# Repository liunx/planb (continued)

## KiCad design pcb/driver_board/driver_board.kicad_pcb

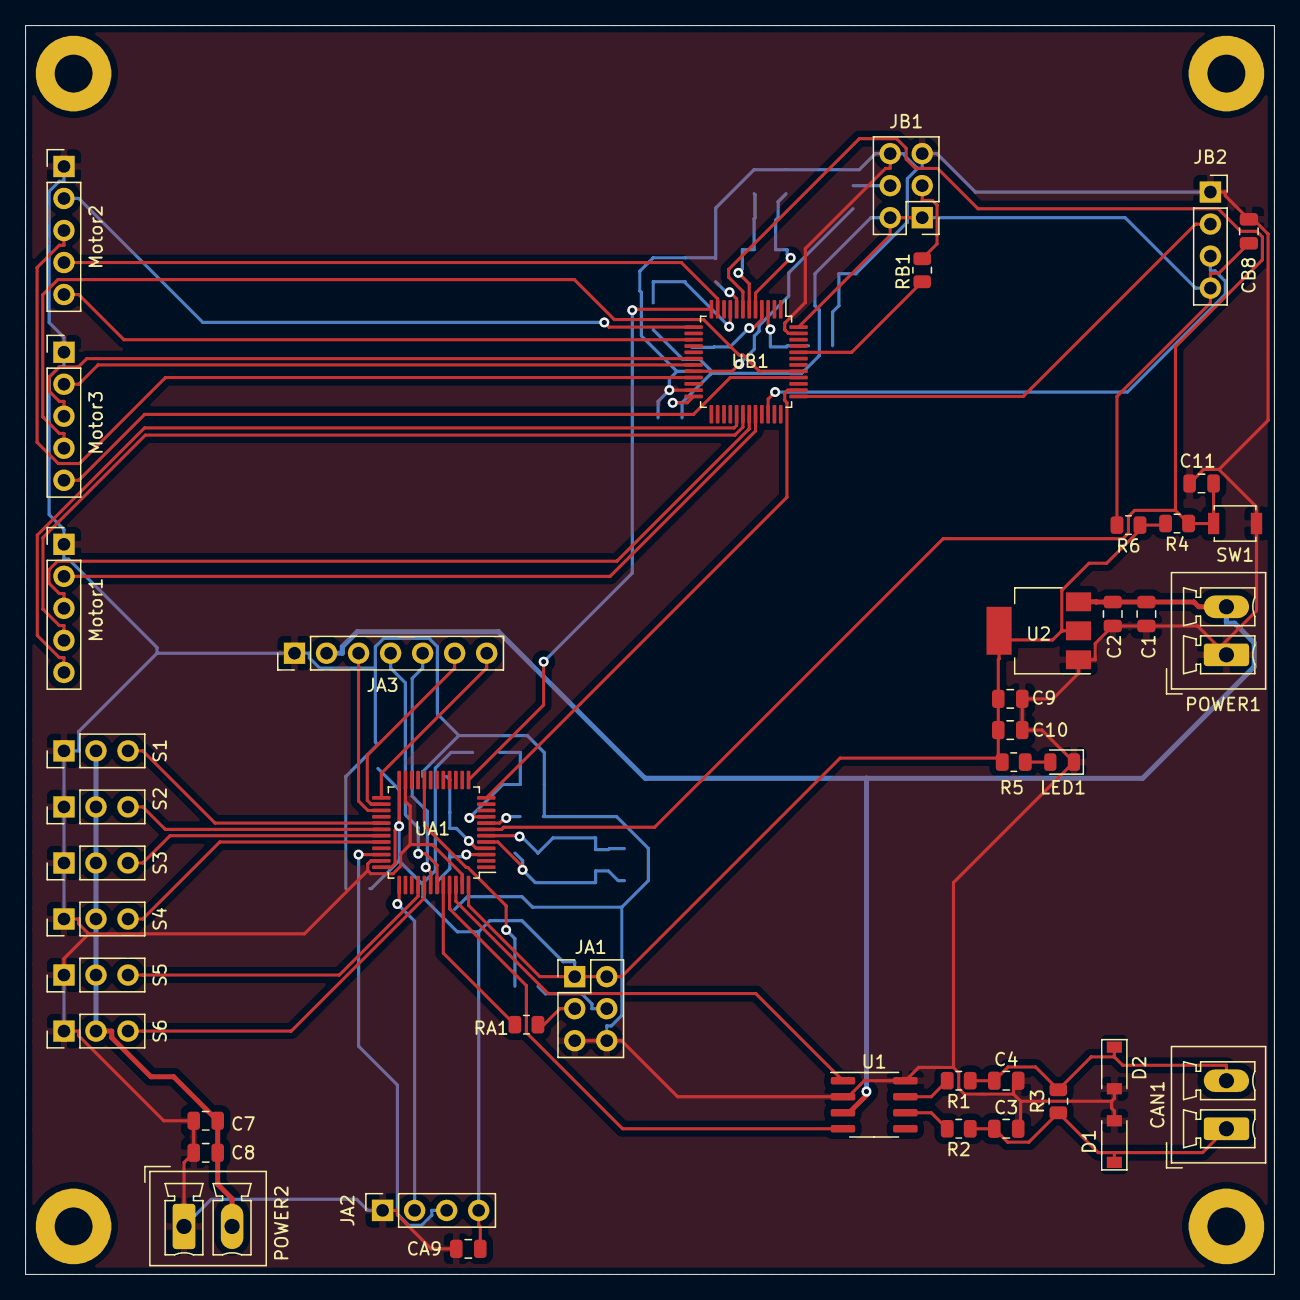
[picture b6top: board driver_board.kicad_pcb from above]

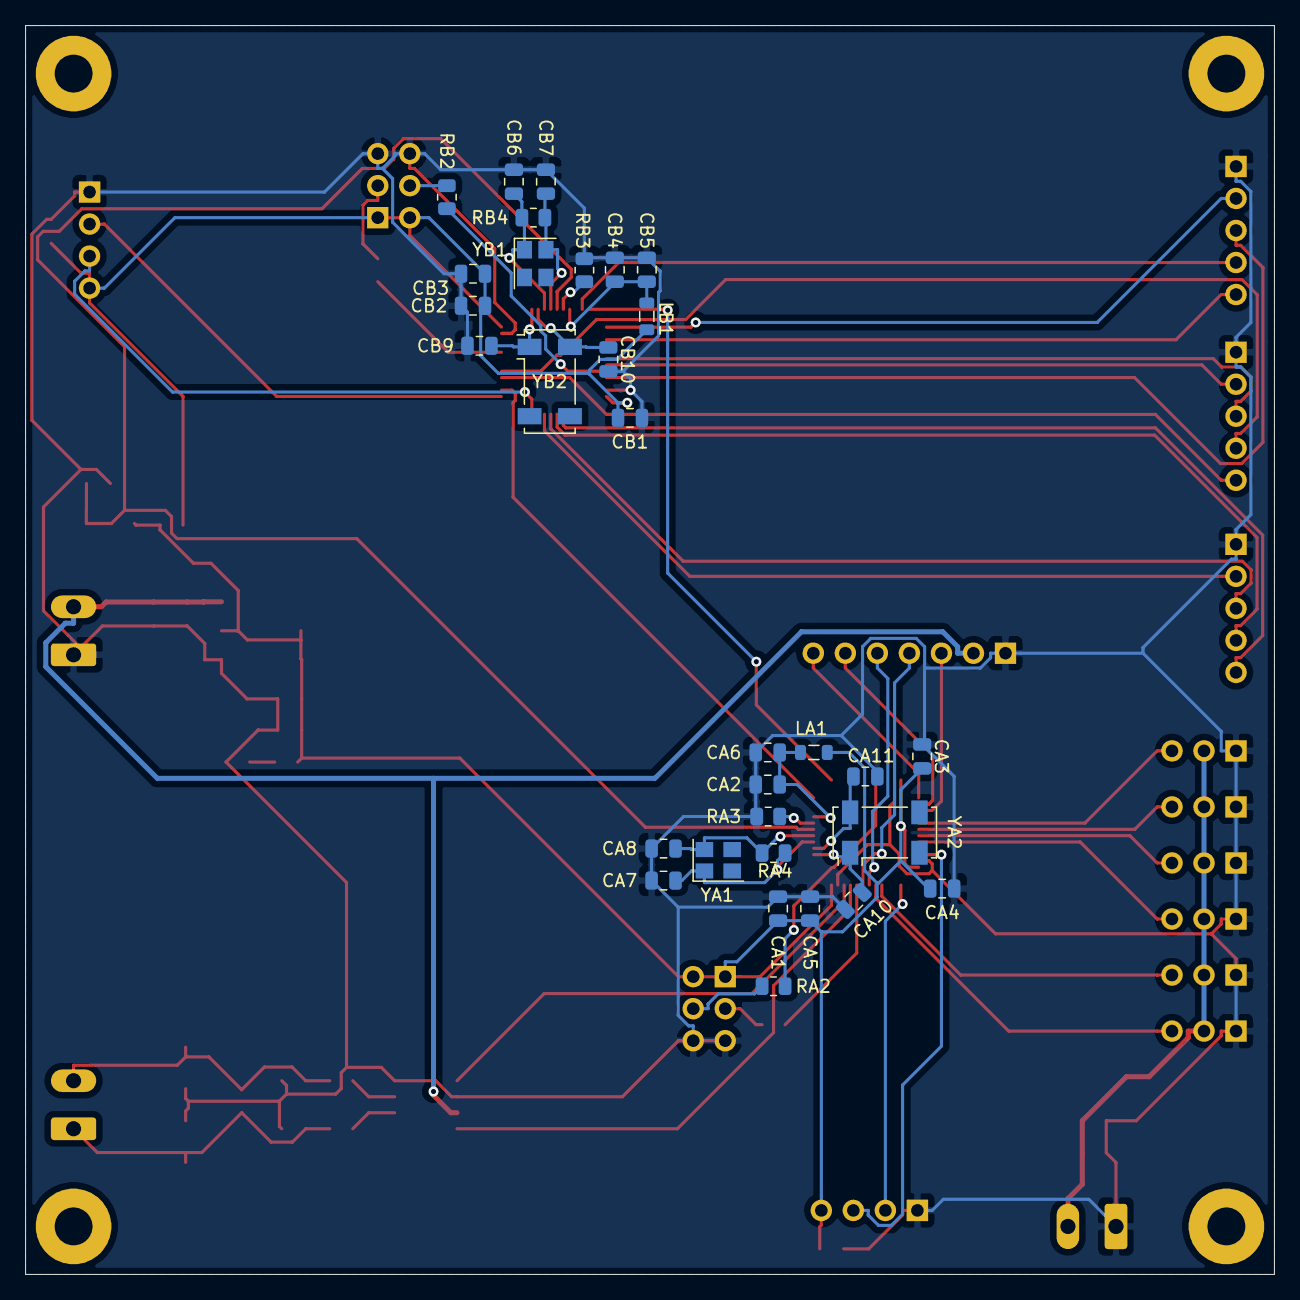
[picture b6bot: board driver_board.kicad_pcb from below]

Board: 2 copper layers, 99.1 x 99.1 mm, 79 parts (31 on the bottom side), 62 nets.

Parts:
C1, C7, C9: 10uF; C_0805_2012Metric
C2, C8, C10: 0.1uF; C_0805_2012Metric
C3, C4: 22pF; C_0805_2012Metric
C11: 10pF; C_0805_2012Metric
CA1: 4.7uF; C_0805_2012Metric
CA2: 10nF; C_0805_2012Metric
CA3, CA4, CA5, CA9: 0.1uF; C_0805_2012Metric
CA6: 1uF; C_0805_2012Metric
CA7, CA8, CA10, CA11: 20pF; C_0805_2012Metric
CAN1: Conn_01x02; PhoenixContact_MCV_1,5_2-G-3.81_1x02_P3.81mm_Vertical
CB1, CB3, CB8: 0.1uF; C_0805_2012Metric
CB2: 4.7uF; C_0805_2012Metric
CB4: 1uF; C_0805_2012Metric
CB5: 10nF; C_0805_2012Metric
CB6, CB7, CB9, CB10: 20pF; C_0805_2012Metric
D1, D2: 1N5817; D_SOD-123
JA1: Conn_02x03_Odd_Even; PinHeader_2x03_P2.54mm_Vertical
JA2: Conn_01x04; PinSocket_1x04_P2.54mm_Vertical
JA3: Conn_01x07; PinHeader_1x07_P2.54mm_Vertical
JB1: Conn_02x03_Odd_Even; PinHeader_2x03_P2.54mm_Vertical
JB2: Conn_01x04; PinSocket_1x04_P2.54mm_Vertical
LA1: 10uH; L_0805_2012Metric
LB1: 10uH; L_0805_2012Metric
LED1: LED; LED_0805_2012Metric
Motor1, Motor2, Motor3: Conn_01x05; PinHeader_1x05_P2.54mm_Vertical
POWER1, POWER2: Conn_01x02; PhoenixContact_MCV_1,5_2-G-3.81_1x02_P3.81mm_Vertical
Pad1, Pad2, Pad3, Pad4: MountingHole_3mm_Pad
R1, R2: 33R; R_0805_2012Metric
R3: 120R; R_0805_2012Metric
R4: 10K; R_0805_2012Metric
R5: 510R; R_0805_2012Metric
R6: 0R; R_0805_2012Metric
RA1, RA2: 100K; R_0805_2012Metric
RA3: 0R; R_0805_2012Metric
RA4: 10M; R_0805_2012Metric
RB1, RB2: 100K; R_0805_2012Metric
RB3: 0R; R_0805_2012Metric
RB4: 10M; R_0805_2012Metric
S1, S2, S3, S4, S5, S6: Conn_01x03; PinHeader_1x03_P2.54mm_Vertical
SW1: SW_Push; SW_SPST_B3U-1000P
U1: TJA1051T; SOIC-8_3.9x4.9mm_P1.27mm
U2: AMS1117-3.3; SOT-223-3_TabPin2
UA1: STM32F103C6Tx; LQFP-48_7x7mm_P0.5mm
UB1: STM32F031C6Tx; LQFP-48_7x7mm_P0.5mm
YA1: 8M; Crystal_SMD_Abracon_ABM8G-4Pin_3.2x2.5mm
YA2: 32768HZ; Crystal_SMD_Abracon_ABS25-4Pin_8.0x3.8mm
YB1: 8M; Crystal_SMD_Abracon_ABM8G-4Pin_3.2x2.5mm
YB2: 32768HZ; Crystal_SMD_Abracon_ABS25-4Pin_8.0x3.8mm

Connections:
+3.3V: C9.1, C10.1, CA1.1, CA3.1, CA4.1, CA5.1, CA9.1, JA1.1, JA1.2, JA2.4, LA1.2, R4.2, R5.2, R6.1, U2.2, UA1.24, UA1.36, UA1.48
+3.3V_F031: CB1.1, CB2.1, CB3.1, CB8.1, JB1.1, JB1.2, JB2.4, LB1.2, R6.2, UB1.24, UB1.48
+5V: C1.1, C2.1, JA3.2, POWER1.2, U1.3, U2.3
+VDC: C7.1, C8.1, POWER2.2, S1.2, S2.2, S3.2, S4.2, S5.2, S6.2
/CANH: C4.1, CAN1.2, D2.1, R1.1, R3.2
/CANL: C3.1, CAN1.1, D1.1, R2.1, R3.1
/Sheet6121200E/3.3VA: CA2.1, CA6.1, LA1.1, UA1.9
/Sheet6121200E/AUX: JA3.3, UA1.27
/Sheet6121200E/BOOT0: RA1.2, UA1.44
/Sheet6121200E/BOOT1: RA2.1, UA1.20
/Sheet6121200E/GNDA: RA3.2, UA1.8
/Sheet6121200E/MD0: JA3.7, UA1.25
/Sheet6121200E/MD1: JA3.6, UA1.26
/Sheet6121200E/RCC_OSC32_IN: CA10.2, UA1.3, YA2.1
/Sheet6121200E/RCC_OSC32_OUT: CA11.2, UA1.4, YA2.4
/Sheet6121200E/RCC_OSC_IN: CA7.2, RA4.2, UA1.5, YA1.1
/Sheet6121200E/RCC_OSC_OUT: CA8.2, RA4.1, UA1.6, YA1.4
/Sheet6121200E/SYS_JTCK-SWCL: JA2.2, UA1.37
/Sheet6121200E/SYS_JTMS-SWDIO: JA2.3, UA1.34
/Sheet6121200E/TIM1_CH1: S1.3, UA1.29
/Sheet6121200E/TIM1_CH2: S2.3, UA1.30
/Sheet6121200E/TIM1_CH3: S3.3, UA1.31
/Sheet6121200E/TIM1_CH4: S4.3, UA1.32
/Sheet6121200E/TIM3_CH1: S5.3, UA1.40
/Sheet6121200E/TIM3_CH2: S6.3, UA1.41
/Sheet6121200E/USART1_RX: JA3.4, UA1.43
/Sheet6121200E/USART1_TX: JA3.5, UA1.42
/sheet61233186/3.3VA: CB4.1, CB5.1, LB1.1, UB1.9
/sheet61233186/BOOT0: RB1.2, UB1.44
/sheet61233186/BOOT1: RB2.1, UB1.20
/sheet61233186/F031_RX: UA1.12, UB1.38
/sheet61233186/F031_TX: UA1.13, UB1.12
/sheet61233186/GNDA: RB3.2, UB1.8
/sheet61233186/RCC_OSC32_IN: CB9.2, UB1.3, YB2.1
/sheet61233186/RCC_OSC32_OUT: CB10.2, UB1.4, YB2.4
/sheet61233186/RCC_OSC_IN: CB6.2, RB4.2, UB1.5, YB1.1
/sheet61233186/RCC_OSC_OUT: CB7.2, RB4.1, UB1.6, YB1.4
/sheet61233186/SYS_JTCK-SWCL: JB2.2, UB1.37
/sheet61233186/SYS_JTMS-SWDIO: JB2.3, UB1.34
/sheet61233186/TIM1_CH1: Motor1.5, UB1.29
/sheet61233186/TIM1_CH2: Motor1.4, UB1.30
/sheet61233186/TIM1_CH3: Motor1.3, UB1.31
/sheet61233186/TIM1_CH4: Motor1.2, UB1.32
/sheet61233186/TIM2_CH1: Motor2.5, UB1.15
/sheet61233186/TIM2_CH2: Motor2.4, UB1.11
/sheet61233186/TIM2_CH3: Motor2.3, UB1.21
/sheet61233186/TIM2_CH4: Motor2.2, UB1.13
/sheet61233186/TIM3_CH1: Motor3.5, UB1.40
/sheet61233186/TIM3_CH2: Motor3.4, UB1.41
/sheet61233186/TIM3_CH3: Motor3.3, UB1.18
/sheet61233186/TIM3_CH4: Motor3.2, UB1.19
CAN_RX: U1.4, UA1.45
CAN_TX: U1.1, UA1.46
GND: C1.2, C2.2, C3.2, C4.2, C7.2, C8.2, C9.2, C10.2, C11.2, CA1.2, CA2.2, CA3.2, CA4.2, CA5.2, CA6.2, CA7.1, CA8.1, CA9.2, CA10.1, CA11.1, CB1.2, CB2.2, CB3.2, CB4.2, CB5.2, CB6.1, CB7.1, CB8.2, CB9.1, CB10.1, D1.2, D2.2, JA1.5, JA1.6, JA2.1, JA3.1, JB1.5, JB1.6, JB2.1, LED1.1, Motor1.1, Motor2.1, Motor3.1, POWER1.1, POWER2.1, RA3.1, RB3.1, S1.1, S2.1, S3.1, S4.1, S5.1, S6.1, SW1.1, U1.2, U1.8, U2.1, UA1.23, UA1.35, UA1.47, UB1.23, UB1.47
unnamed: JA1.3, RA1.1
unnamed: JA1.4, RA2.2
unnamed: JB1.3, RB1.1
unnamed: JB1.4, RB2.2
unnamed: LED1.2, R5.1
unnamed: R1.2, U1.7
unnamed: R2.2, U1.6
RESET: C11.1, R4.1, SW1.2, UA1.7, UB1.7

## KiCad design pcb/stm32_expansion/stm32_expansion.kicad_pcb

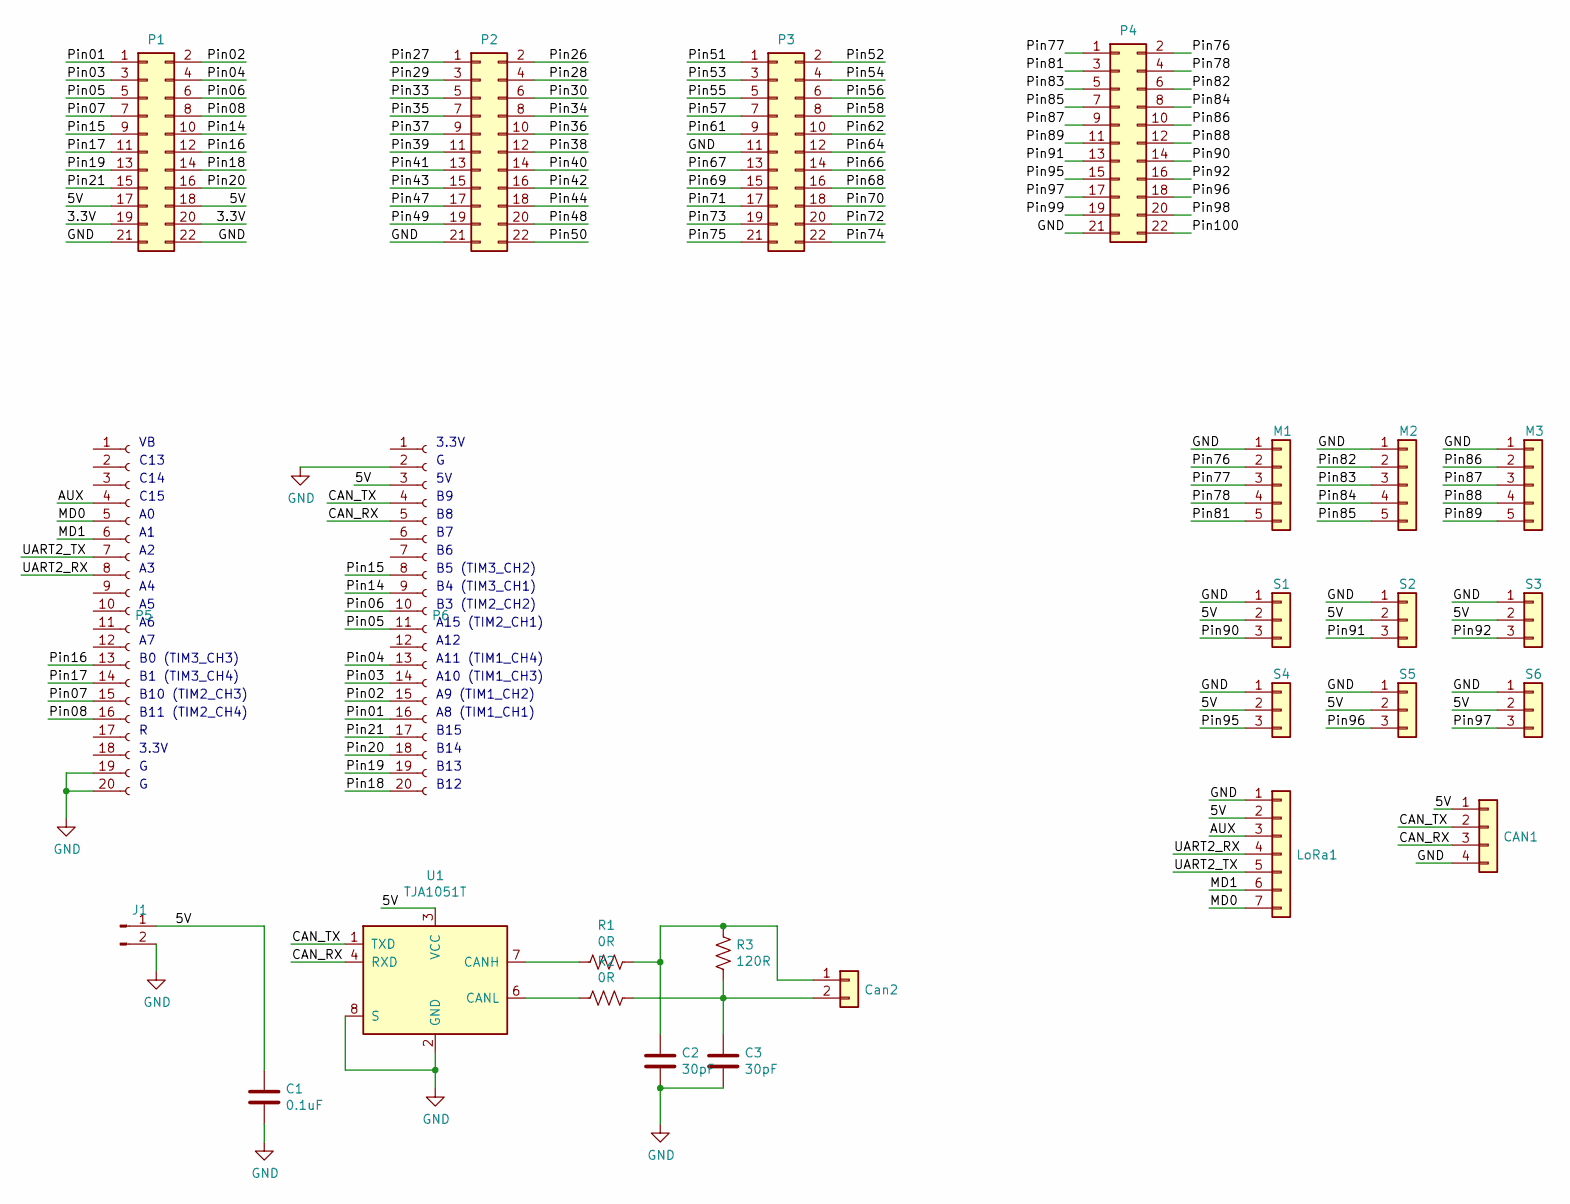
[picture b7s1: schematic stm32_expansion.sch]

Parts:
C1: 0.1uF; CP_EIA-2012-12_Kemet-R
C2, C3: 30pF; CP_EIA-2012-12_Kemet-R
CAN1: Conn_01x04; PinSocket_1x04_P2.54mm_Vertical
Can2: Conn_01x02; PinSocket_1x02_P2.54mm_Vertical
J1: Conn_01x02_Male; PinSocket_1x02_P2.54mm_Vertical
LoRa1: Conn_01x07; PinSocket_1x07_P2.54mm_Vertical
M1, M2, M3: Conn_01x05; PinSocket_1x05_P2.54mm_Vertical
P1, P2, P3, P4: Conn_02x11_Odd_Even; PinSocket_2x11_P2.54mm_Vertical
P5, P6: Conn_01x20_Female; PinSocket_1x20_P2.54mm_Vertical
R1, R2: 0R; R_0805_2012Metric
R3: 120R; R_0805_2012Metric
S1, S2, S3, S4, S5, S6: Conn_01x03; PinSocket_1x03_P2.54mm_Vertical
U1: TJA1051T; SOIC-8_3.9x4.9mm_P1.27mm

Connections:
/3.3V: P1.19, P1.20
/5V: C1.1, CAN1.1, J1.1, LoRa1.2, P1.17, P1.18, P6.3, S1.2, S2.2, S3.2, S4.2, S5.2, S6.2, U1.3 (VCC)
/AUX: LoRa1.3, P5.4
/CAN_RX: CAN1.3, P6.5, U1.4 (RXD)
/CAN_TX: CAN1.2, P6.4, U1.1 (TXD)
/MD0: LoRa1.7, P5.5
/MD1: LoRa1.6, P5.6
/Pin01: P1.1, P6.16
/Pin02: P1.2, P6.15
/Pin03: P1.3, P6.14
/Pin04: P1.4, P6.13
/Pin05: P1.5, P6.11
/Pin06: P1.6, P6.10
/Pin07: P1.7, P5.15
/Pin08: P1.8, P5.16
/Pin14: P1.10, P6.9
/Pin15: P1.9, P6.8
/Pin16: P1.12, P5.13
/Pin17: P1.11, P5.14
/Pin18: P1.14, P6.20
/Pin19: P1.13, P6.19
/Pin20: P1.16, P6.18
/Pin21: P1.15, P6.17
/Pin26: P2.2
/Pin27: P2.1
/Pin28: P2.4
/Pin29: P2.3
/Pin30: P2.6
/Pin33: P2.5
/Pin34: P2.8
/Pin35: P2.7
/Pin36: P2.10
/Pin37: P2.9
/Pin38: P2.12
/Pin39: P2.11
/Pin40: P2.14
/Pin41: P2.13
/Pin42: P2.16
/Pin43: P2.15
/Pin44: P2.18
/Pin47: P2.17
/Pin48: P2.20
/Pin49: P2.19
/Pin50: P2.22
/Pin51: P3.1
/Pin52: P3.2
/Pin53: P3.3
/Pin54: P3.4
/Pin55: P3.5
/Pin56: P3.6
/Pin57: P3.7
/Pin58: P3.8
/Pin61: P3.9
/Pin62: P3.10
/Pin64: P3.12
/Pin66: P3.14
/Pin67: P3.13
/Pin68: P3.16
/Pin69: P3.15
/Pin70: P3.18
/Pin71: P3.17
/Pin72: P3.20
/Pin73: P3.19
/Pin74: P3.22
/Pin75: P3.21
/Pin76: M1.2, P4.2
/Pin77: M1.3, P4.1
/Pin78: M1.4, P4.4
/Pin81: M1.5, P4.3
/Pin82: M2.2, P4.6
/Pin83: M2.3, P4.5
/Pin84: M2.4, P4.8
/Pin85: M2.5, P4.7
/Pin86: M3.2, P4.10
/Pin87: M3.3, P4.9
/Pin88: M3.4, P4.12
/Pin89: M3.5, P4.11
/Pin90: P4.14, S1.3
/Pin91: P4.13, S2.3
/Pin92: P4.16, S3.3
/Pin95: P4.15, S4.3
/Pin96: P4.18, S5.3
/Pin97: P4.17, S6.3
/Pin98: P4.20
/Pin99: P4.19
/Pin100: P4.22
/UART2_RX: LoRa1.4, P5.8
/UART2_TX: LoRa1.5, P5.7
GND: C1.2, C2.2, C3.2, CAN1.4, J1.2, LoRa1.1, M1.1, M2.1, M3.1, P1.21, P1.22, P2.21, P3.11, P4.21, P5.19, P5.20, P6.2, S1.1, S2.1, S3.1, S4.1, S5.1, S6.1, U1.2 (GND), U1.8 (S)
unnamed: C2.1, Can2.1, R1.1, R3.2
unnamed: C3.1, Can2.2, R2.1, R3.1
unnamed: R1.2, U1.7 (CANH)
unnamed: R2.2, U1.6 (CANL)

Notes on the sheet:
C13
C14
C15
B0 (TIM3_CH3)
B1 (TIM3_CH4)
B10 (TIM2_CH3)
B11 (TIM2_CH4)
3.3V
B5 (TIM3_CH2)
B4 (TIM3_CH1)
B3 (TIM2_CH2)
A15 (TIM2_CH1)
A12
A11 (TIM1_CH4)
A10 (TIM1_CH3)
A9 (TIM1_CH2)
A8 (TIM1_CH1)
B15
B14
B13
B12

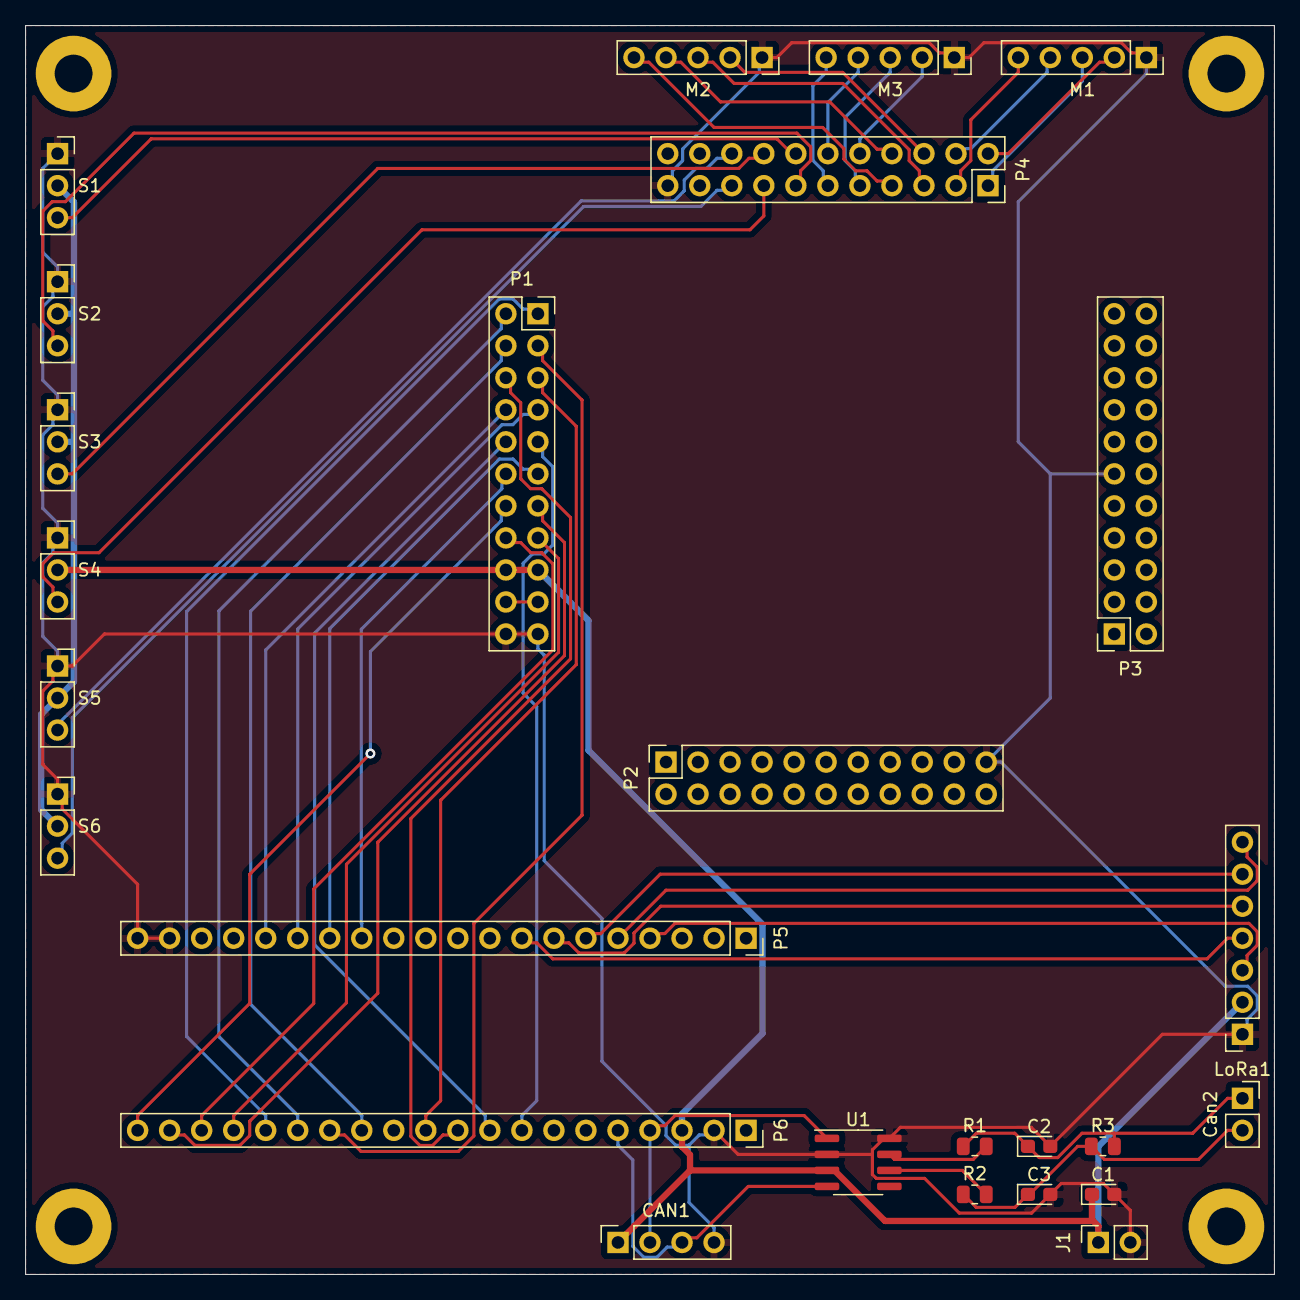
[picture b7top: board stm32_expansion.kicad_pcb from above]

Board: 2 copper layers, 99.1 x 99.1 mm, 30 parts (0 on the bottom side), 48 nets.

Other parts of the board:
Pad1, Pad2, Pad3, Pad4: MountingHole_3mm_Pad

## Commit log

2021-05-21 temple files
2021-05-27 Add labeler.py for collect dataset.
2021-05-27 Remove temple files.
2021-05-27 Add frame shrink.
2021-05-27 Add rotation support.
2021-05-27 Add viewer.py for review dataset.
2021-05-27 Resize max height/width.
2021-05-29 Update tracker to support multiple tracking.
2021-06-09 add finder.
2021-06-09 add aruco_markers.py.
2021-06-15 add more feature to finder.py.
2021-06-15 add tracker and marker.
2021-06-16 update finder.py.
2021-06-16 update create_markers for finder.py.
2021-06-17 add optical flow support.
2021-06-18 add dense_flow.py.
2021-07-24 Add switcher.
2021-07-27 Add pybind11.
2021-07-27 Update code for pybind11.
2021-07-28 Update tb.py.
2021-07-28 Update switcher.v.
2021-08-05 Add webots simulator.
2021-08-05 Add motors.
2021-08-05 Add ros2 driver for webots.
2021-08-08 Add stm32_expansion pcb.
2021-08-09 Update schematic.
2021-08-09 Update pcb.
2021-08-10 Update pcb layout.
2021-08-10 update uart to lora.
2021-08-10 complete pcb.
2021-08-11 Add U30x30.
2021-08-12 Add U45x25 and S25x25.
2021-08-15 Update parts.
2021-08-18 Add driver board.
2021-08-19 Update Power supply scheme.
2021-08-20 Update layout.
2021-08-23 Complete the driver_board.
2021-08-23 Optimize driver_board.
2021-08-24 Update driver_board.
2021-08-26 Add control_center board.
2021-08-27 Layout control_center board.
2021-08-29 Update layout for control center board.
2021-08-30 Update control center board.
2021-08-30 Add f031_core board.
2021-08-30 Put more components to back.
2021-08-31 Complete f031_core board.
2021-08-31 Add f103_core board.
2021-08-31 Fix layout of f031_core board.
2021-08-31 Update layout of f031 & f103 boards.
2021-08-31 Add routing keypoints for capacitors.
2021-09-03 Add bus_slot.
2021-09-03 Add f031_card board.
2021-09-07 Add controls for robot.
2021-09-10 Update f031_core board.
2021-09-14 Update f103_core board.
2021-09-15 Upadate pcb layout for f103_core board.
2021-09-15 Add more ground vias for f103_core board.
2021-09-16 Remove unused boards.
2021-09-16 Add remote_control board.
2021-09-16 Cleanup unused project.
2021-09-16 Add custom footprints and symbols.
2021-09-16 Update remote_control board.
2021-09-16 Layout remote_control board.
2021-09-17 Update footprint and symbol for remote_control board.
2021-09-18 Complete layout for remote_control board.
2021-09-22 Add driver_board.
2021-10-08 Add tests for robot.
2021-11-10 Add tool for create steering angles and drive powers lookup tables.
